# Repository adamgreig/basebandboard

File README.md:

# basebandboard

Hardware for experimenting with baseband communication techniques and FPGAs.

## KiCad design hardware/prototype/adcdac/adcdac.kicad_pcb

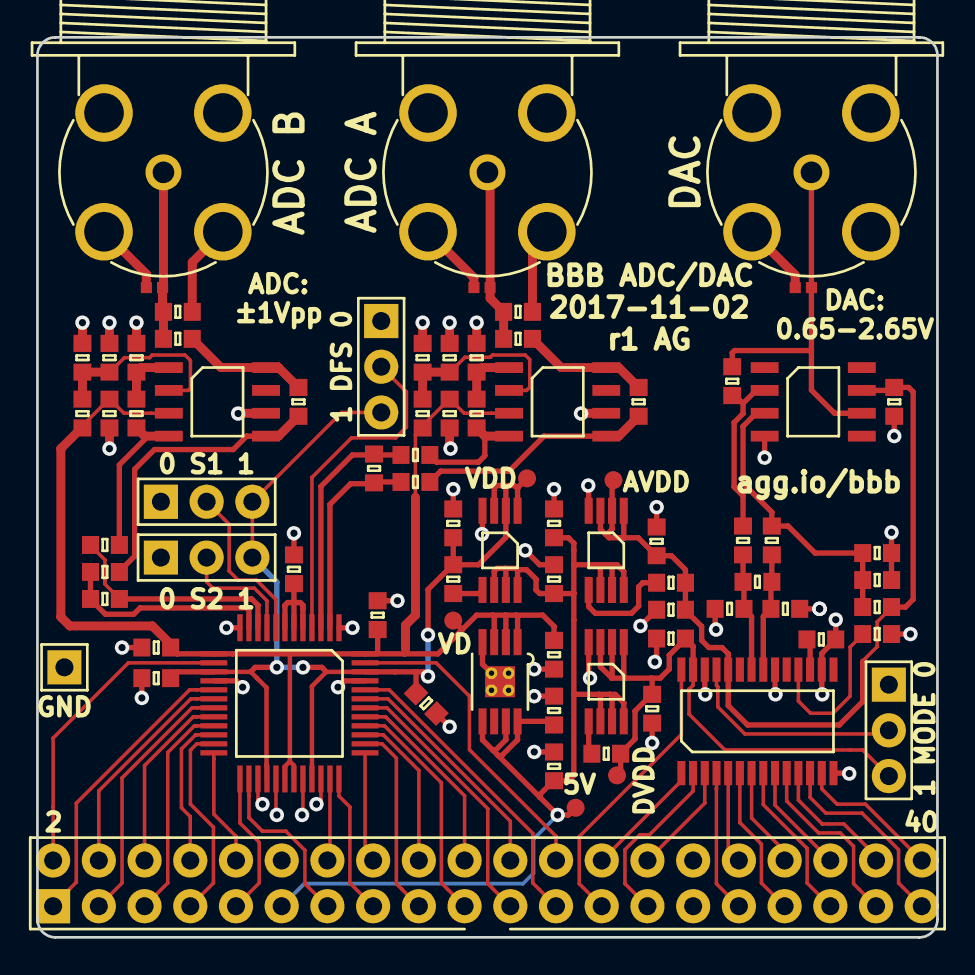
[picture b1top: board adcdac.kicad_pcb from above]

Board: 2 copper layers, 50.0 x 50.0 mm, 80 parts (0 on the bottom side), 73 nets.

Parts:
C1, C5, C7, C9, C13, C14, C19, C20: 1µ; 0603
C2, C4, C6, C11, C16, C18, C21, C22, C23, C24, C25, C26, C27, C28: 100n; 0603
C3, C8, C17: 1n; 0603
C10, C12, C15: 15p; 0603
D1, D2, D3: ESD_DIODE; 0402
IC1, IC4, IC6: ADP3335; MSOP-8
IC2, IC3: AD8138; SOIC-8
IC5: AD9744; TSSOP-28
IC7: ADP124; MSOP-8-EP-AD
IC8: AD8041; SOIC-8
IC9: AD9218; LQFP-48
J1: FPGA_GPIO0; DIL-254P-40
J2: MODE; SIL-254P-03
J3: S2; SIL-254P-03
J4: S1; SIL-254P-03
J5: DFS; SIL-254P-03
J6: GND; SIL-254P-01
P1, P2, P3: COAX; BNC_PCB_RA_5-1634556-0
R1, R5: 50; 0603
R2, R6: 10k; 0603
R3, R7: 5k; 0603
R4, R9, R11, R12, R13, R14, R26: 500; 0603
R8, R10: 525; 0603
R15, R16, R17, R18, R19, R20: 25; 0603
R21: 2k; 0603
R22, R25: 225; 0603
R23, R24: 1k; 0603
TP1, TP2, TP3, TP4, TP5: TESTPAD

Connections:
5v: C1.1, C7.1, C13.1, C14.1, IC1.6, IC1.7, IC1.8, IC4.6, IC4.7, IC4.8, IC6.6, IC6.7, IC6.8, IC7.5, IC7.7, IC7.8, J1.11, TP2.1
/ADC_VD: C18.1, C20.1, C23.1, C25.1, C26.1, IC2.3, IC3.3, IC7.1, IC7.2, IC7.3, IC9.13, IC9.30, IC9.31, IC9.48, R2.2, R6.2, TP5.1
/ADC_VDD: C17.2, C19.1, C24.1, C27.1, IC6.1, IC6.2, IC6.3, IC9.15, IC9.28, IC9.33, IC9.46, J3.3, J4.3, J5.3, TP4.1
/DAC_AVDD: C3.2, C5.1, C6.1, C22.1, IC1.1, IC1.2, IC1.3, IC5.24, IC8.7, R23.2, TP1.1
/DAC_DVDD: C8.2, C9.1, C11.1, IC4.1, IC4.2, IC4.3, IC5.27, J2.3, TP3.1
/GPIO0_00: IC9.14, J1.2
/GPIO0_01: IC9.18, J1.4
/GPIO0_02: IC9.21, J1.5
/GPIO0_03: IC9.20, J1.6
/GPIO0_04: IC9.23, J1.7
/GPIO0_05: IC9.22, J1.8
/GPIO0_06: IC9.25, J1.9
/GPIO0_07: IC9.24, J1.10
/GPIO0_08: IC9.26, J1.13
/GPIO0_09: IC9.35, J1.14
/GPIO0_10: IC9.36, J1.15
/GPIO0_11: IC9.37, J1.16
/GPIO0_12: IC9.38, J1.17
/GPIO0_13: IC9.39, J1.18
/GPIO0_14: IC9.40, J1.19
/GPIO0_15: IC9.41, J1.20
/GPIO0_16: IC9.42, J1.21
/GPIO0_17: IC9.43, J1.22
/GPIO0_18: IC9.44, J1.23
/GPIO0_19: IC9.47, J1.24
/GPIO0_20: IC5.28, J1.25
/GPIO0_21: IC5.1, J1.26
/GPIO0_22: IC5.2, J1.27
/GPIO0_23: IC5.3, J1.28
/GPIO0_24: IC5.4, J1.31
/GPIO0_25: IC5.5, J1.32
/GPIO0_26: IC5.6, J1.33
/GPIO0_27: IC5.7, J1.34
/GPIO0_28: IC5.8, J1.35
/GPIO0_29: IC5.9, J1.36
/GPIO0_30: IC5.10, J1.37
/GPIO0_31: IC5.11, J1.38
/GPIO0_32: IC5.12, J1.39
/GPIO0_33: IC5.13, J1.40
/GPIO0_IN0: IC9.17, J1.1
/GPIO0_IN1: IC9.19, J1.3
GND: C1.2, C2.2, C4.2, C5.2, C6.2, C7.2, C9.2, C11.2, C13.2, C14.2, C16.2, C18.2, C19.2, C20.2, C21.2, C22.2, C23.2, C24.2, C25.2, C26.2, C27.2, C28.2, D1.2, D2.2, D3.2, IC1.4, IC2.6, IC3.6, IC4.4, IC5.14, IC5.16, IC5.20, IC5.26, IC6.4, IC7.4, IC7.EP, IC8.4, IC9.1, IC9.12, IC9.16, IC9.27, IC9.29, IC9.32, IC9.34, IC9.45, J1.12, J1.30, J2.1, J3.1, J4.1, J5.1, J6.1, P1.2, P2.2, P3.2, R1.2, R3.1, R5.2, R7.1, R8.1, R10.1, R19.2, R20.2, R21.2, R24.1
unnamed: C2.1, IC2.2, R2.1, R3.2
unnamed: C3.1, IC1.5
unnamed: C4.1, IC3.2, R6.1, R7.2
unnamed: C8.1, IC4.5
unnamed: C10.1, IC9.2, R15.1
unnamed: C10.2, IC9.3, R16.1
unnamed: C12.1, IC9.11, R17.1
unnamed: C12.2, IC9.10, R18.1
unnamed: C15.1, IC5.21, R19.1, R25.2
unnamed: C15.2, IC5.22, R20.1, R22.2
unnamed: C16.1, IC5.17
unnamed: C17.1, IC6.5
unnamed: C21.1, IC9.5, IC9.6, IC9.7
unnamed: C28.1, IC8.3, R23.1, R24.2, R25.1
unnamed: D1.1, P1.1, R1.1, R4.2
unnamed: D2.1, P2.1, R5.1, R9.2
unnamed: D3.1, IC8.6, P3.1, R26.1
unnamed: IC2.1, R8.2, R12.1
unnamed: IC2.4, R12.2, R16.2
unnamed: IC2.5, R11.2, R15.2
unnamed: IC2.8, R4.1, R11.1
unnamed: IC3.1, R10.2, R14.1
unnamed: IC3.4, R14.2, R18.2
unnamed: IC3.5, R13.2, R17.2
unnamed: IC3.8, R9.1, R13.1
unnamed: IC5.18, R21.1
unnamed: IC5.25, J2.2
unnamed: IC8.2, R22.1, R26.2
unnamed: IC9.4, J5.2
unnamed: IC9.8, J4.2
unnamed: IC9.9, J3.2

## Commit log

2017-10-31 Initial commit.
2017-10-31 Add PRBS-k generator
2017-11-01 first go at prototype ADC/DAC hardware
2017-11-01 Minor sch tweaks
2017-11-02 finish routing, order r1 boards
2017-11-03 assign part numbers, generate bom
2017-11-04 Add first go at LUT-OPT implementation. Search code coming later.
2017-11-06 first roll of rust gf2 code for finding good recurrence matrices
2017-11-06 remove old berlekamp_massey version
2017-11-09 more or less working polynomial modulus multiplication
2017-11-10 add primitivity testing, yay
2017-11-10 tidy up primitivity test
2017-11-10 bring it all together into a recurrence-finding machine. beta.
2017-11-11 fix subtle stupid bugs, now finds n>32 max-period recurrences yay
2017-11-11 add verify py script
2017-11-11 fix last bugs, can now v quickly find v large matrices, yay!
2017-11-13 write out dieharder-suitable random entries for testing
2017-11-13 add some example matrices and packing script
2017-11-13 add one more example matrix
2017-11-13 add CLT-GRNG FHDL
2017-11-13 add quick de0nano test script
2017-11-13 correct output bitlength of cltgrng
2017-11-15 Add cool PRBSShaper. Still need to work out a good way to test it.
2017-11-15 add effective test for prbsshaper
2017-11-18 add stickerbom and paste stencil
2017-11-18 reorganise gateware, prep first actual fpga spin
2017-11-19 add pll to clock dac up to 200MS/s
2017-11-19 add some early testing results from dac
2017-11-19 update prototype adcdac board sch to new kicad version
2017-11-19 add a few more thermal pics
2017-11-22 add NCO and example usage
2017-11-22 add delayline and moving average
2017-11-24 put together rx prototype
2017-11-24 add nco testing result images
2017-11-27 add uart in/out utilities
2017-11-27 fix error in moving average filter, apparently
2017-11-28 it works!!
2017-11-28 add new scripts and result plots etc
2017-12-16 add axi3 slave read/write
2017-12-16 add software for axi3 testing
2017-12-18 try adding interrupts fpga->hps
2017-12-23 wip2
2017-12-30 wip sdram controller
2017-12-30 add axi3 two/from bram
2017-12-31 fixes to sdram controller. now works. include demo.
2017-12-31 tidyup sdram demo
2018-01-01 simple lcd demo working
2018-01-01 wip lcd
2018-01-02 working lcd and touch screen
2018-01-12 add axi3 read mux
2018-01-12 add lcd double buffer
2018-01-12 update axi3 read mux test to test simultaneous attempts
2018-01-12 add axi3 write mux
2018-01-15 add 16x sinc interpolator
2018-01-15 add done output to interpolator
2018-01-16 add AXI3ToFromBRAM and refactor old BRAMToAXI3 and AXI3ToBRAM to use it
2018-01-16 working ui and touch, sweet!
2018-11-06 [old files] draw ui
2018-11-06 [old files] font generation
2018-11-07 ui now controls tx completely
2018-11-07 fix sdram tests (i hope)
2018-11-07 fix prbs error detector test
2018-11-07 reduce tx clock rate to get more adc samples per bit
2018-11-08 rearrange Top
2018-11-08 Add DSO class
2018-11-08 display works!!!
